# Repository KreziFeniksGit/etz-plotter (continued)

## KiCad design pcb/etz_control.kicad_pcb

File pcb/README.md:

# Main control PCB (KiCad 10)

**Current design (23 Oct): three split single-sided boards, hand-routed - see split_boards.md** (drivers/, power/, controller/).
The single-board files below (etz_control.*) are the earlier versions, kept for reference.

**Current version: HOME (single-sided, toner transfer), placed, NOT routed - Egor routes it by hand (22 Oct).**
`build_pcb.py` has `HOME = True`: 169 x 136 mm, copper on the bottom only, traces >= 0.5 mm (signals 0.6, 5 V 1.2, motors 1.0,
power 2.0), 0.6 mm gaps (0.8 around power), oval 1.7 x 2.6 pads with 1.0 mm drills on 2.54 mm rows (round 1.9 on the 2x5 header),
1206 parts and the SMD parts on the copper side, IRLZ44N (TO-220) instead of the SOT-23 MOSFET. DRC with these rules: 0 errors.
The auto-router could not do it single-sided (66 wire jumpers + 70 drilled holes and still 9 open): route by hand.
Tips for routing by hand:
- Route power first (VBAT, VDRIVE, GND), then motors, then signals. Leave GND for a ground pour at the end (Place > Zone, B.Cu).
- Where a trace cannot cross, use a wire jumper on the top side: drill two holes, insulated wire, solder underneath.
- **You may swap ESP32 pins** to remove crossings (the firmware is not written yet). Allowed GPIOs: 1, 2, 4..18, 21, 39..42, 47
  (38 only if your board is v1.0). A_IO and VBAT_SENSE must stay on GPIO 1..10 (ADC1). Never use 0, 3, 19, 20, 26..37, 43..46, 48.
  Tell Claude which pins you moved: wiring.md, the schematic and the firmware follow.
- For printing: File > Plot, layer B.Cu + Edge.Cuts, PDF, black, scale 1:1, drill marks "small"; NOT mirrored for the bottom layer
  (the toner transfer itself mirrors it the right way).

| File | What |
|---|---|
| `bom.md` | every part on and off the board, the power tree, what is still VERIFY |
| `build_pcb.py` | parts, nets (from `wiring.md`), placement, JLCPCB rules, net classes -> routes with Freerouting -> GND pours + stitching vias |
| `etz_control.kicad_pcb` | the board (open it in KiCad) |
| `etz_control.kicad_sch` + `etz_control_schematic.pdf` | **full connection schematic** (KiCad + PDF), A2; `schematic_preview.png` |
| `build_sch.py` | makes the schematic from the same parts/nets as `build_pcb.py`, then checks: KiCad netlist == board nets, ERC, PDF |
| `etz.kicad_sym`, `etz.pretty/`, `sym-lib-table`, `fp-lib-table` | project library: symbols + footprints of the plug-in modules (ESP32-S3-DevKitC-1, TMC2209, Mini560 Pro, BSS138) |
| `etz_control_gerbers_jlcpcb.zip` | upload this to JLCPCB / PCBWay (Gerbers + drill), 2 layers, 1.6 mm, 1 oz |
| `render_top.png`, `render_bottom.png`, `copper.svg` | pictures |
| `drc.json` | KiCad design-rule check result |

Rebuild: `"C:\Program Files\KiCad\10.0\bin\python.exe" pcb\build_pcb.py` (about 3 min: routing), then
`kicad-cli pcb drc --refill-zones pcb\etz_control.kicad_pcb`, then the Gerber / drill export (see the end of this file).
Routing needs Java 25 + Freerouting 2.5 in `%USERPROFILE%\tools` (`jre25\`, `freerouting-2.5.0.jar`).

## v1.0 (22 Oct): 130 x 105 mm, 2 layers, 69 footprints, 58 nets, fully routed
DRC: 0 unconnected, 0 clearance errors. Remaining warnings (accepted): the XT60 / XT30 outlines cross the board edge on purpose
(the plug goes in from the edge); 3 GND pins (U1B pin 1, U8A/U8B pin 4) have 1 thermal spoke instead of 2 - they are also
joined by a trace.

## Review checklist (from JLCPCB / Altium / DigiKey / TI layout guides) and how this board meets it
| Check | Status |
|---|---|
| DRC set to the fab's limits, not KiCad defaults | min track / clearance 0.15, via 0.6 / 0.3 drill, hole-to-hole 0.5, copper to edge 0.4 (JLCPCB standard is 0.127 / 0.3) |
| Trace width by current (IPC-2152, ~10 C rise) | VBAT / VDRIVE 1.5 mm (~4 A), 5 V rails 1.0 mm, motor phases 0.8 mm (0.9 A), signals 0.3 mm |
| Bulk capacitor close to each driver's VM | C1..C4 100 uF directly below each TMC2209 |
| Servo rail spike capacitor | C5 470 uF + C6 100 nF next to the servo rail |
| Solid ground | GND pour on both layers, 44 stitching vias, thermal reliefs for hand soldering |
| Footprints match the real parts | KiCad standard library; module pinouts VERIFY (below) |
| Polarity marked | + on electrolytics and XT plugs, K bar on diodes, pin 1 marks on headers |
| Labels | every connector named on the silkscreen; board name + version |
| Test points | 3V3, +5V, +5V servo, GND |
| Mounting | 4x M3 holes, 4 mm from the corners |
| Protection | main 5 A fuse inline; 0.5 A PTC on connector C's V pin; flyback diode on the magnet; EN pull-up keeps drivers off at boot; gate pull-down keeps the magnet off |
| Auto-router output reviewed | 0 unrouted; power traces checked wide; see renders |
| Not applicable | antenna keep-out (the radio is never used), impedance control, fiducials (hand assembly) |

## VERIFY before ordering (guesses about bought modules)
ESP32-S3-DevKitC-1 pin rows (22.86) and pinout revision (v1.1 has its RGB LED on GPIO38 = TOF XSHUT here); TMC2209 V1.3
pin order; Mini560 Pro pad positions (IN at one end, OUT 25.4 mm away - measure yours); motor
connector pin order (match your motor cables); XT60 / XT30 genders. A photo of each module with a ruler settles them.

## Export commands
```
kicad-cli pcb export gerbers --layers F.Cu,B.Cu,F.Mask,B.Mask,F.Silkscreen,B.Silkscreen,Edge.Cuts --subtract-soldermask -o pcb/fab/ pcb/etz_control.kicad_pcb
kicad-cli pcb export drill --format excellon --excellon-units mm --excellon-separate-th -o pcb/fab/ pcb/etz_control.kicad_pcb
```

## Making your own PCB from the schematic
Open `etz_control.kicad_pro`, open the schematic, then Tools > Update PCB from Schematic (F8) into a NEW board (or delete the
footprints in the existing one first: the generated board uses two sockets per module, the schematic one footprint per module).
Footprints are already assigned. Net classes (track widths) are in the project: Power 1.5 mm, Rail5V 1.0, Motor 0.8, signals 0.3.

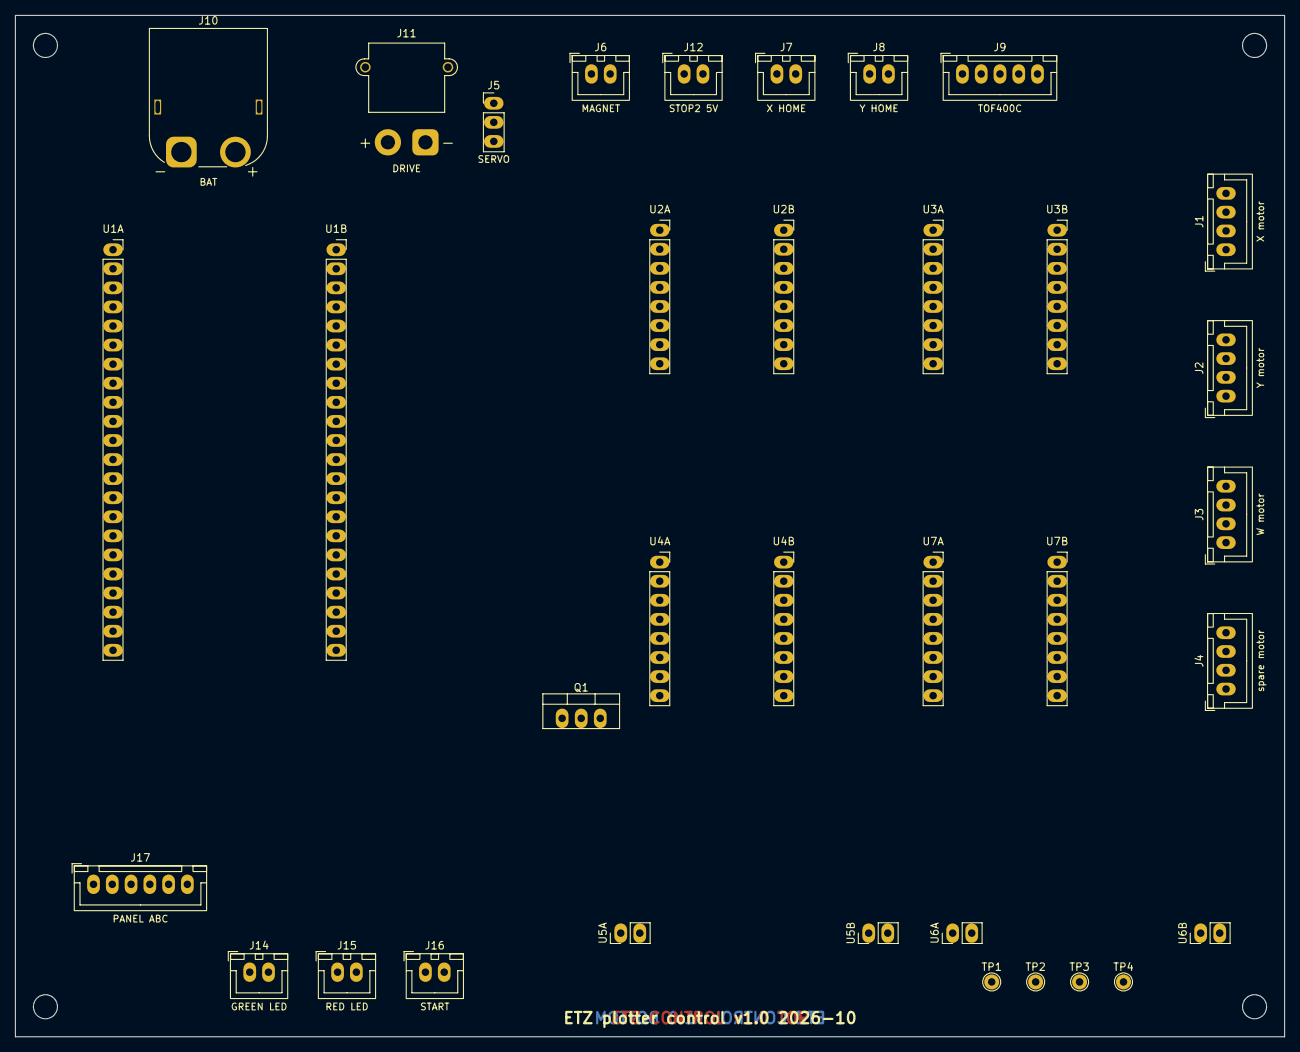
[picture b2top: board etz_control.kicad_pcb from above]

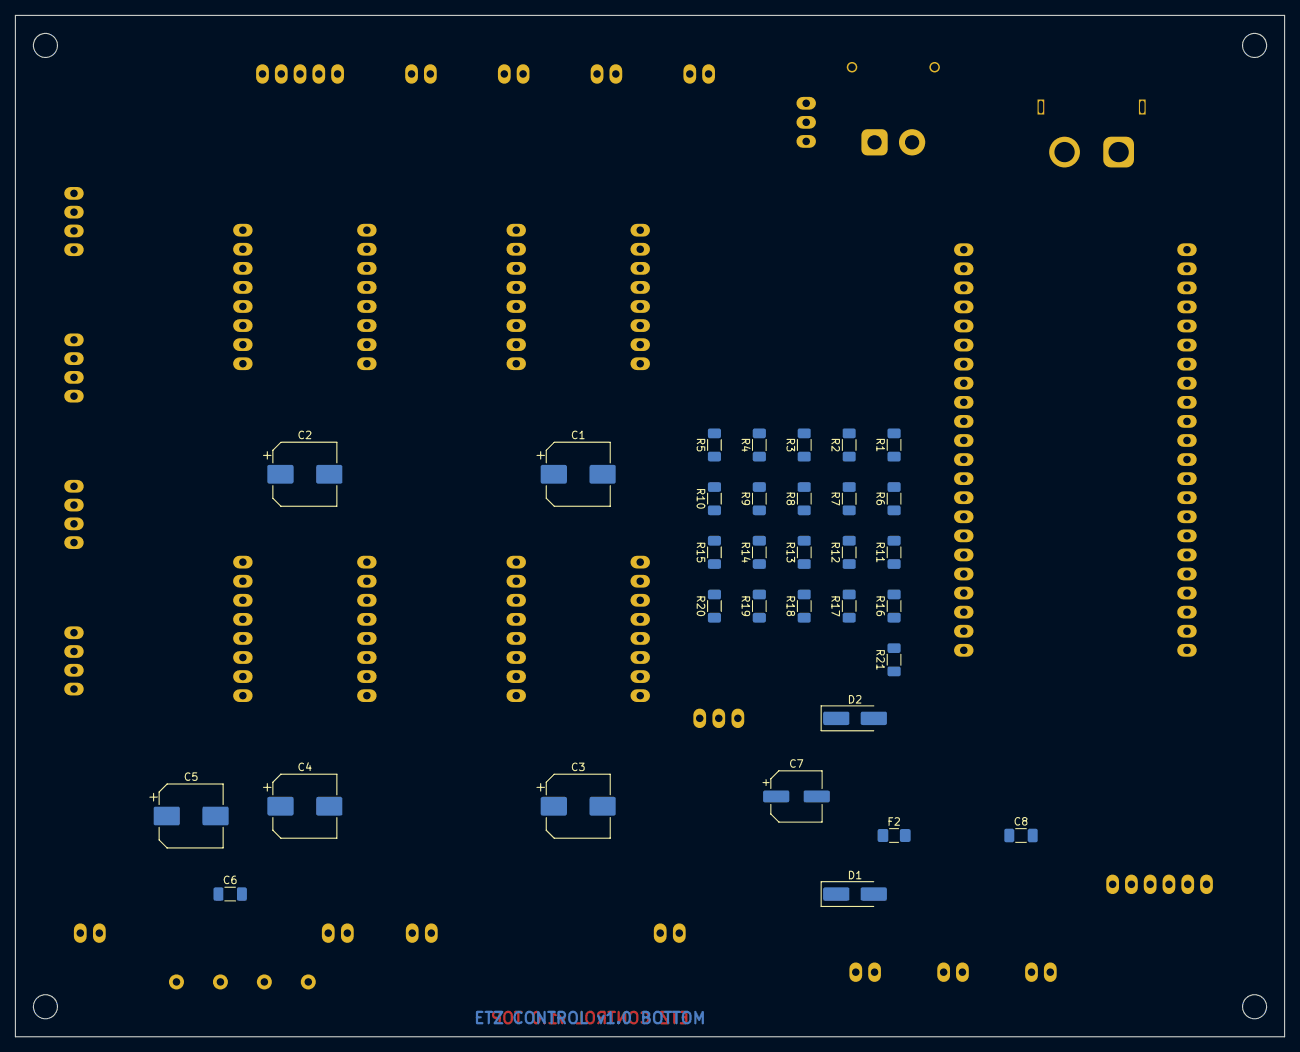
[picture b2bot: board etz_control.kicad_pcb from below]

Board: 2 copper layers, 169.0 x 136.0 mm, 71 parts (32 on the bottom side), 58 nets, no tracks yet.

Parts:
C1, C2, C3, C4: 100uF 35V; CP_Elec_8x10
C5: 470uF 16V; CP_Elec_8x10
C6: 100nF; C_1206_3216Metric_Pad1.33x1.80mm_HandSolder
C7: 100uF 10V; CP_Elec_6.3x7.7
C8: 10nF; C_1206_3216Metric_Pad1.33x1.80mm_HandSolder
D1: SS34; D_SMA_Handsoldering
D2: SS34 flyback; D_SMA_Handsoldering
F2: PTC 0.5A; Fuse_1206_3216Metric_Pad1.42x1.75mm_HandSolder
H1, H2, H3, H4: M3; MountingHole_3.2mm_M3
J1: X motor; JST_XH_B4B-XH-A_1x04_P2.50mm_Vertical
J2: Y motor; JST_XH_B4B-XH-A_1x04_P2.50mm_Vertical
J3: W motor; JST_XH_B4B-XH-A_1x04_P2.50mm_Vertical
J4: spare motor; JST_XH_B4B-XH-A_1x04_P2.50mm_Vertical
J5: SERVO; PinHeader_1x03_P2.54mm_Vertical
J6: MAGNET; JST_XH_B2B-XH-A_1x02_P2.50mm_Vertical
J7: X HOME; JST_XH_B2B-XH-A_1x02_P2.50mm_Vertical
J8: Y HOME; JST_XH_B2B-XH-A_1x02_P2.50mm_Vertical
J9: TOF400C; JST_XH_B5B-XH-A_1x05_P2.50mm_Vertical
J10: BAT; AMASS_XT60PW-M_1x02_P7.20mm_Horizontal
J11: DRIVE; AMASS_XT30PW-M_1x02_P2.50mm_Horizontal
J12: STOP2 5V; JST_XH_B2B-XH-A_1x02_P2.50mm_Vertical
J14: GREEN LED; JST_XH_B2B-XH-A_1x02_P2.50mm_Vertical
J15: RED LED; JST_XH_B2B-XH-A_1x02_P2.50mm_Vertical
J16: START; JST_XH_B2B-XH-A_1x02_P2.50mm_Vertical
J17: PANEL ABC; JST_XH_B6B-XH-A_1x06_P2.50mm_Vertical
Q1: IRLZ44N; TO-220-3_Vertical
R1, R3, R15: 100k; R_1206_3216Metric_Pad1.30x1.75mm_HandSolder
R2: 22k; R_1206_3216Metric_Pad1.30x1.75mm_HandSolder
R4: 15k; R_1206_3216Metric_Pad1.30x1.75mm_HandSolder
R5, R7, R10, R11, R19: 10k; R_1206_3216Metric_Pad1.30x1.75mm_HandSolder
R6, R20, R21: 20k; R_1206_3216Metric_Pad1.30x1.75mm_HandSolder
R8, R9, R18: 1k; R_1206_3216Metric_Pad1.30x1.75mm_HandSolder
R12, R13: 4.7k; R_1206_3216Metric_Pad1.30x1.75mm_HandSolder
R14: 100R; R_1206_3216Metric_Pad1.30x1.75mm_HandSolder
R16: 1.5k 0.25W; R_1206_3216Metric_Pad1.30x1.75mm_HandSolder
R17: 220R; R_1206_3216Metric_Pad1.30x1.75mm_HandSolder
TP1: 3V3; TestPoint_THTPad_D2.0mm_Drill1.0mm
TP2: +5V; TestPoint_THTPad_D2.0mm_Drill1.0mm
TP3: +5VS; TestPoint_THTPad_D2.0mm_Drill1.0mm
TP4: GND; TestPoint_THTPad_D2.0mm_Drill1.0mm
U1A: ESP32-S3 J1; PinSocket_1x22_P2.54mm_Vertical
U1B: ESP32-S3 J3; PinSocket_1x22_P2.54mm_Vertical
U2A: TMC2209 X left; PinSocket_1x08_P2.54mm_Vertical
U2B: TMC2209 X right; PinSocket_1x08_P2.54mm_Vertical
U3A: TMC2209 Y left; PinSocket_1x08_P2.54mm_Vertical
U3B: TMC2209 Y right; PinSocket_1x08_P2.54mm_Vertical
U4A: TMC2209 W left; PinSocket_1x08_P2.54mm_Vertical
U4B: TMC2209 W right; PinSocket_1x08_P2.54mm_Vertical
U5A: Mini560 Pro 5V logic IN; PinHeader_1x02_P2.54mm_Vertical
U5B: Mini560 Pro 5V logic OUT; PinHeader_1x02_P2.54mm_Vertical
U6A: Mini560 Pro 5V servo IN; PinHeader_1x02_P2.54mm_Vertical
U6B: Mini560 Pro 5V servo OUT; PinHeader_1x02_P2.54mm_Vertical
U7A: TMC2209 S left; PinSocket_1x08_P2.54mm_Vertical
U7B: TMC2209 S right; PinSocket_1x08_P2.54mm_Vertical

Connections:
3V3: J9.1, R10.2, R11.2, R12.2, R13.2, TP1.1, U1A.1, U1A.2, U2B.7, U3A.2, U3B.7, U4A.3, U4B.7, U7A.2, U7A.3, U7B.7
5V_ESP: D1.1, U1A.21
+5V: C7.1, D1.2, F2.1, J12.1, TP2.1, U5B.1
+5VS: C5.1, C6.1, J5.2, TP3.1, U6B.1
A_IO: C8.1, R7.2, R21.1, U1B.4
A_SIG: J17.1, R7.1
B_IO: R5.2, R6.1, U1A.16
B_SIG: J17.2, R5.1
C_RX: J17.4, R19.1
C_TX: J17.3, R18.2
C_V: F2.2, J17.5
DRV_EN: R10.1, U1A.19, U2A.1, U3A.1, U4A.1, U7A.1
GND: C1.2, C2.2, C3.2, C4.2, C5.2, C6.2, C7.2, C8.2, J5.3, J7.2, J8.2, J9.2, J10.1, J11.2, J14.2, J15.2, J16.2, J17.6, Q1.3, R2.2, R4.2, R6.2, R15.2, R20.2, R21.2, TP4.1, U1A.22, U1B.1, U1B.21, U1B.22, U2A.2, U2A.3, U2B.2, U2B.8, U3A.3, U3B.2, U3B.8, U4A.2, U4B.2, U4B.8, U5A.2, U5B.2, U6A.2, U6B.2, U7B.2, U7B.8
LEDG_A: J14.1, R16.2
LEDR_A: J15.1, R17.2
LEDR_IO: R17.1, U1B.6
MAG5: D2.1, J6.1, J12.2
MAG_G: Q1.1, R14.2, R15.1
MAG_IO: R14.1, U1B.18
MAG_SW: D2.2, J6.2, Q1.2
SCL: J9.4, R13.1, U1A.18
SDA: J9.3, R12.1, U1A.17
SERVO_IO: R9.1, U1A.20
SERVO_SIG: J5.1, R9.2
START: J16.1, U1B.7
STOP_SENSE: R1.2, R2.1, U1B.17
S_1A: J4.1, U7B.5
S_1B: J4.2, U7B.6
S_2A: J4.3, U7B.4
S_2B: J4.4, U7B.3
TMC_TX: R8.1, U1A.8
TMC_UART: R8.2, U1A.9, U2A.4, U3A.4, U4A.4, U7A.4
TOF_XSHUT: J9.5, R11.1, U1B.10
U1_RX: R19.2, R20.1, U1A.11
U1_TX: R18.1, U1A.10
VBAT: J10.2, R3.1, U5A.1
VBAT_SENSE: R3.2, R4.1, U1B.5
VDRIVE: C1.1, C2.1, C3.1, C4.1, J11.1, R1.1, R16.1, U2B.1, U3B.1, U4B.1, U6A.1, U7B.1
W_1A: J3.1, U4B.5
W_1B: J3.2, U4B.6
W_2A: J3.3, U4B.4
W_2B: J3.4, U4B.3
W_DIR: U1A.15, U4A.8
W_STEP: U1A.12, U4A.7
X_1A: J1.1, U2B.5
X_1B: J1.2, U2B.6
X_2A: J1.3, U2B.4
X_2B: J1.4, U2B.3
X_DIR: U1A.5, U2A.8
X_HOME: J7.1, U1B.9
X_STEP: U1A.4, U2A.7
Y_1A: J2.1, U3B.5
Y_1B: J2.2, U3B.6
Y_2A: J2.3, U3B.4
Y_2B: J2.4, U3B.3
Y_DIR: U1A.7, U3A.8
Y_HOME: J8.1, U1B.8
Y_STEP: U1A.6, U3A.7

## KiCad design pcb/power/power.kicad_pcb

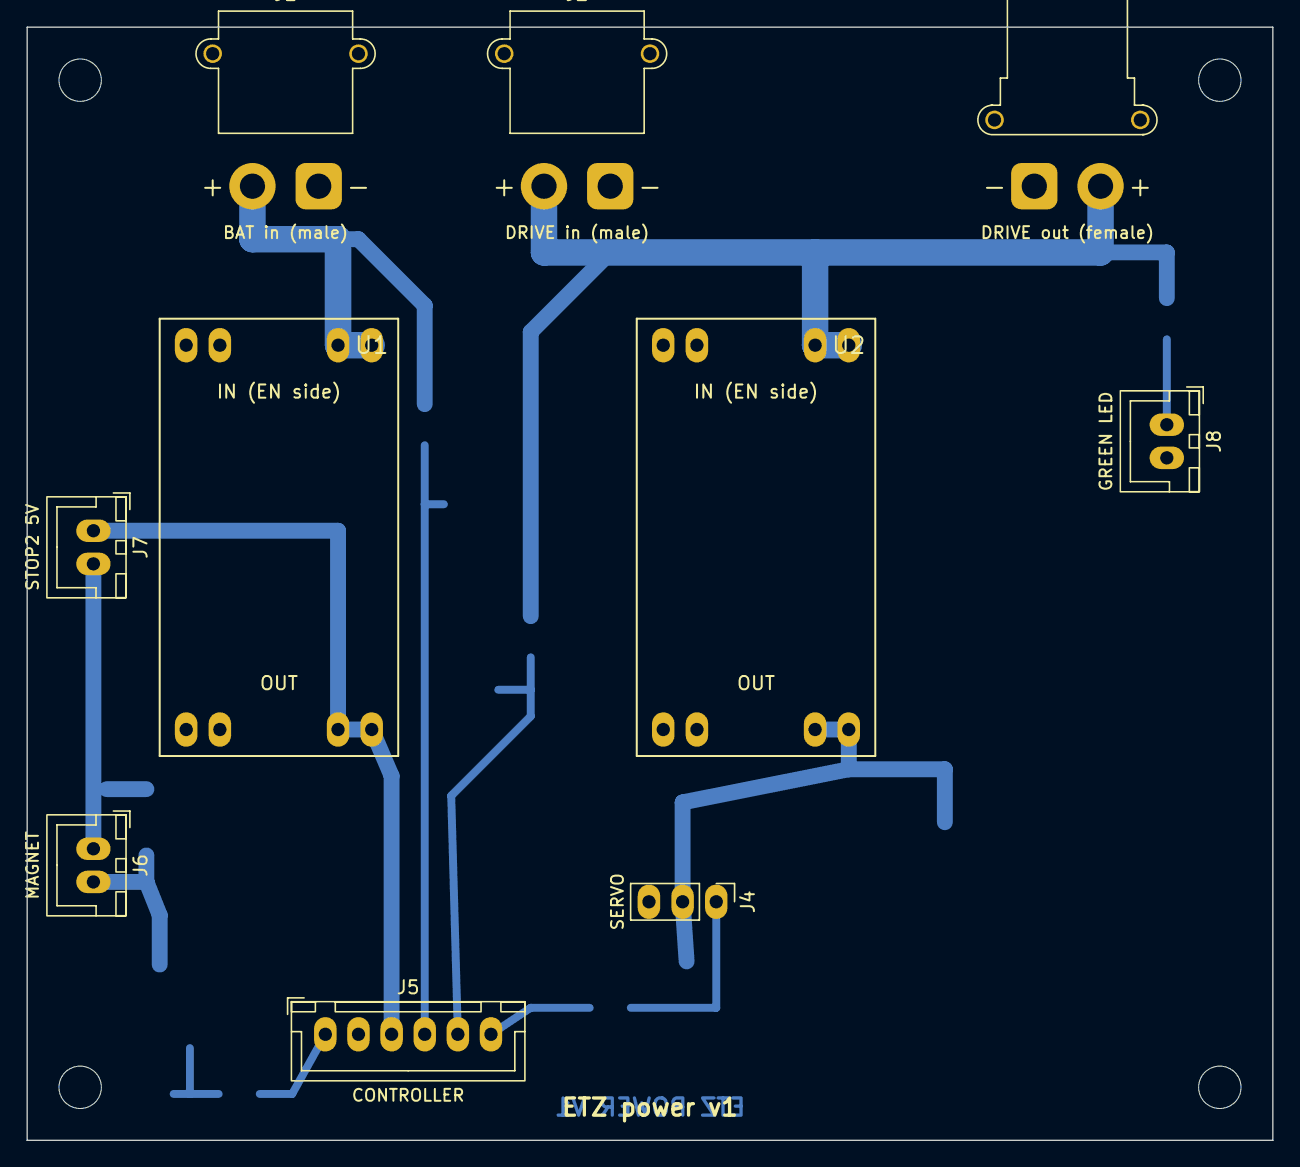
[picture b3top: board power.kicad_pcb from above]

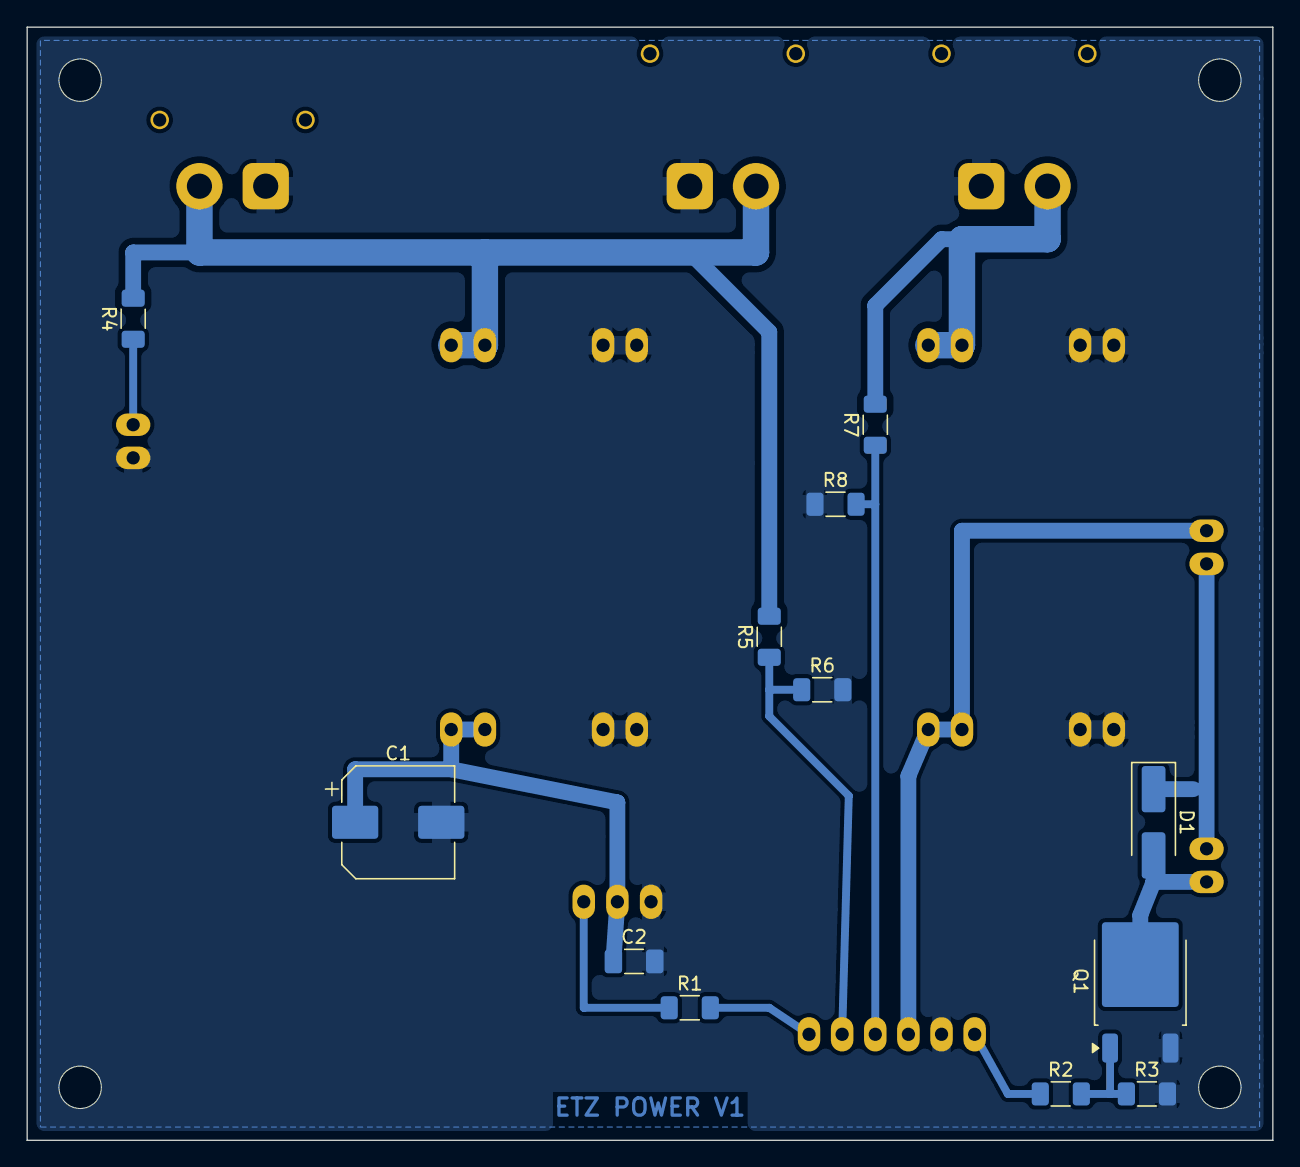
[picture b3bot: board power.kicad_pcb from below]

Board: 2 copper layers, 94.0 x 84.0 mm, 26 parts (12 on the bottom side), 14 nets.

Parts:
C1: 470uF 16V; CP_Elec_8x10
C2: 100nF; C_1206_3216Metric_Pad1.33x1.80mm_HandSolder
D1: SS34 flyback; D_SMA_Handsoldering
H1, H2, H3, H4: M3; MountingHole_3.2mm_M3
J1: BAT in (male); AMASS_XT30PW-M_1x02_P2.50mm_Horizontal
J2: DRIVE in (male); AMASS_XT30PW-M_1x02_P2.50mm_Horizontal
J3: DRIVE out (female); AMASS_XT30PW-F_1x02_P2.50mm_Horizontal
J4: SERVO; PinHeader_1x03_P2.54mm_Vertical
J5: CONTROLLER; JST_XH_B6B-XH-A_1x06_P2.50mm_Vertical
J6: MAGNET; JST_XH_B2B-XH-A_1x02_P2.50mm_Vertical
J7: STOP2 5V; JST_XH_B2B-XH-A_1x02_P2.50mm_Vertical
J8: GREEN LED; JST_XH_B2B-XH-A_1x02_P2.50mm_Vertical
Q1: 100N03A; TO-252-2
R1: 1k; R_1206_3216Metric_Pad1.30x1.75mm_HandSolder
R2: 100R; R_1206_3216Metric_Pad1.30x1.75mm_HandSolder
R3, R5, R7: 100k; R_1206_3216Metric_Pad1.30x1.75mm_HandSolder
R4: 1.5k; R_1206_3216Metric_Pad1.30x1.75mm_HandSolder
R6: 22k; R_1206_3216Metric_Pad1.30x1.75mm_HandSolder
R8: 15k; R_1206_3216Metric_Pad1.30x1.75mm_HandSolder
U1: Mini560 Pro 5V logic
U2: Mini560 Pro 5V servo

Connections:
+5V: J5.3, J7.1, U1.3
+5VS: C1.1, C2.1, J4.2, U2.3
GND: C1.2, C2.2, J1.1, J2.1, J3.1, J4.3, J5.2, J8.2, Q1.3, R3.2, R6.2, R8.1, U1.2, U1.4, U2.2, U2.4
LEDG_A: J8.1, R4.1
MAG5: D1.1, J6.1, J7.2
MAG_G: Q1.1, R2.2, R3.1
MAG_IO: J5.1, R2.1
MAG_SW: D1.2, J6.2, Q1.2
SERVO_IO: J5.6, R1.2
SERVO_SIG: J4.1, R1.1
STOP_SENSE: J5.5, R5.1, R6.1
VBAT: J1.2, R7.2, U1.1
VBAT_SENSE: J5.4, R7.1, R8.2
VDRIVE: J2.2, J3.2, R4.2, R5.2, U2.1

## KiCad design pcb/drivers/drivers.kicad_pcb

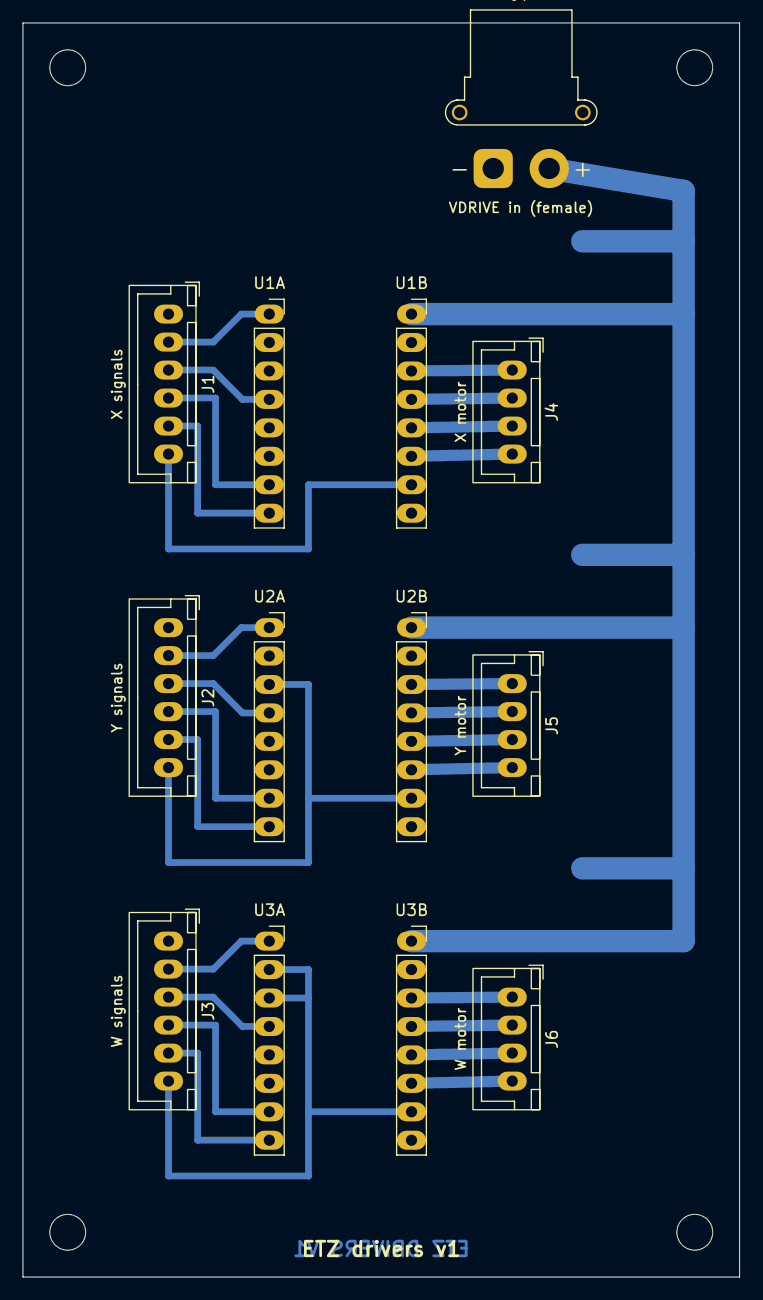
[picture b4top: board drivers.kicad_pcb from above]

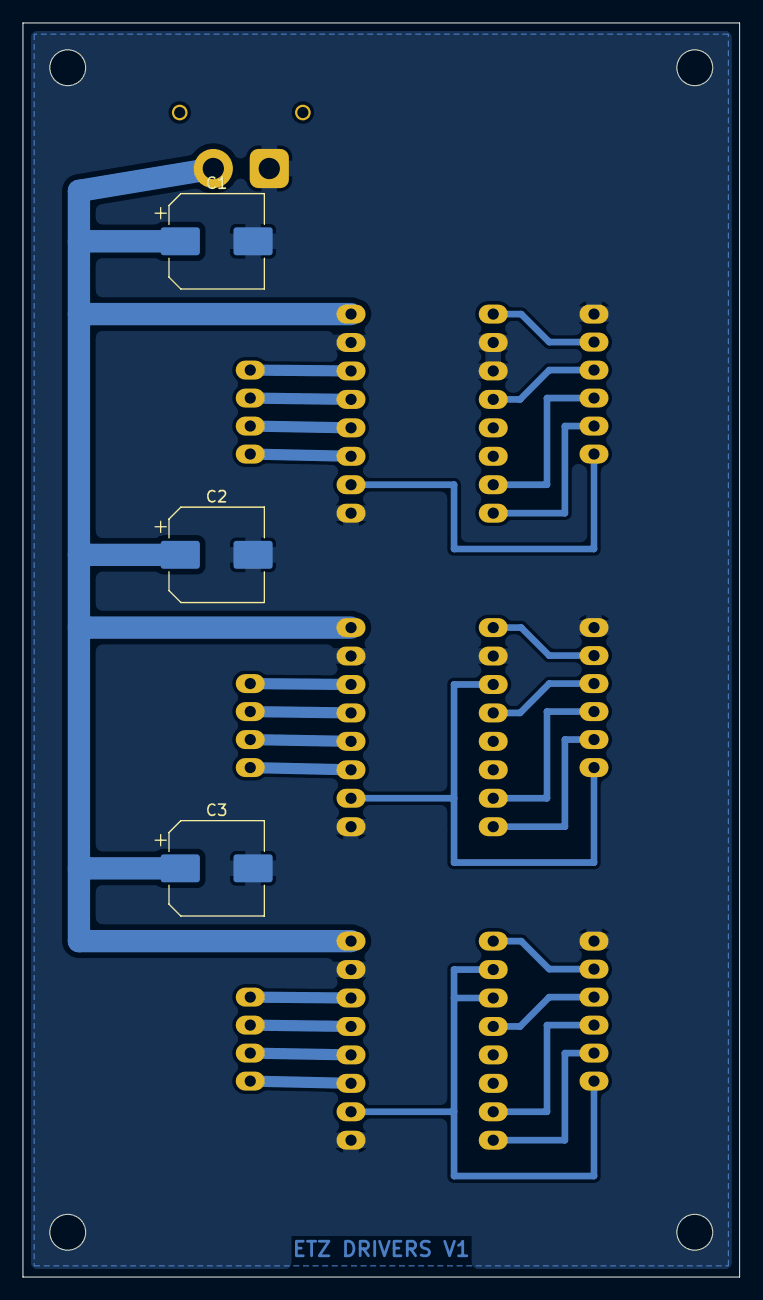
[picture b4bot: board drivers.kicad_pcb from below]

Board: 2 copper layers, 64.0 x 112.0 mm, 20 parts (3 on the bottom side), 29 nets.

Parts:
C1, C2, C3: 100uF 25V; CP_Elec_8x10
H1, H2, H3, H4: M3; MountingHole_3.2mm_M3
J1: X signals; JST_XH_B6B-XH-A_1x06_P2.50mm_Vertical
J2: Y signals; JST_XH_B6B-XH-A_1x06_P2.50mm_Vertical
J3: W signals; JST_XH_B6B-XH-A_1x06_P2.50mm_Vertical
J4: X motor; JST_XH_B4B-XH-A_1x04_P2.50mm_Vertical
J5: Y motor; JST_XH_B4B-XH-A_1x04_P2.50mm_Vertical
J6: W motor; JST_XH_B4B-XH-A_1x04_P2.50mm_Vertical
J7: VDRIVE in (female); AMASS_XT30PW-F_1x02_P2.50mm_Horizontal
U1A, U1B: TMC2209 X; PinSocket_1x08_P2.54mm_Vertical
U2A, U2B: TMC2209 Y; PinSocket_1x08_P2.54mm_Vertical
U3A, U3B: TMC2209 W; PinSocket_1x08_P2.54mm_Vertical

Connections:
GND: C1.2, C2.2, C3.2, J1.1, J2.1, J3.1, J7.1, U1A.2, U1A.3, U1B.2, U1B.8, U2A.2, U2B.2, U2B.8, U3B.2, U3B.8
VDRIVE: C1.1, C2.1, C3.1, J7.2, U1B.1, U2B.1, U3B.1
W_1A: J6.3, U3B.5
W_1B: J6.4, U3B.6
W_2A: J6.2, U3B.4
W_2B: J6.1, U3B.3
W_3V3: J3.6, U3A.2, U3A.3, U3B.7
W_DIR: J3.5, U3A.8
W_EN: J3.2, U3A.1
W_STEP: J3.4, U3A.7
W_UART: J3.3, U3A.4
X_1A: J4.3, U1B.5
X_1B: J4.4, U1B.6
X_2A: J4.2, U1B.4
X_2B: J4.1, U1B.3
X_3V3: J1.6, U1B.7
X_DIR: J1.5, U1A.8
X_EN: J1.2, U1A.1
X_STEP: J1.4, U1A.7
X_UART: J1.3, U1A.4
Y_1A: J5.3, U2B.5
Y_1B: J5.4, U2B.6
Y_2A: J5.2, U2B.4
Y_2B: J5.1, U2B.3
Y_3V3: J2.6, U2A.3, U2B.7
Y_DIR: J2.5, U2A.8
Y_EN: J2.2, U2A.1
Y_STEP: J2.4, U2A.7
Y_UART: J2.3, U2A.4

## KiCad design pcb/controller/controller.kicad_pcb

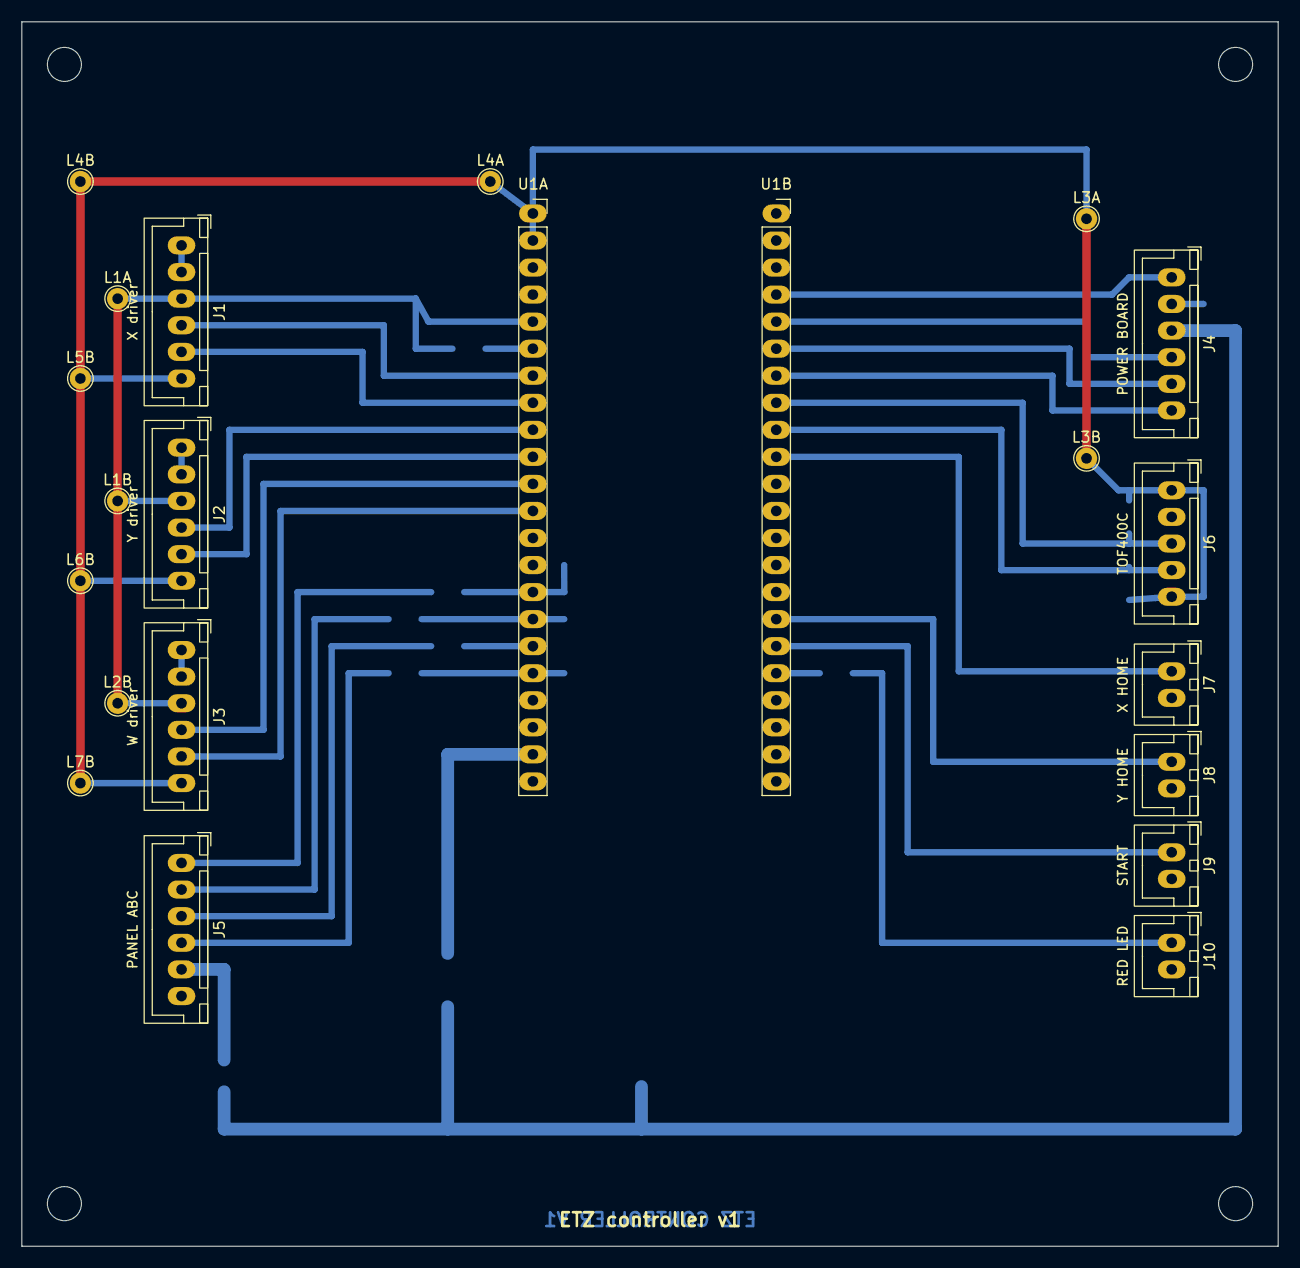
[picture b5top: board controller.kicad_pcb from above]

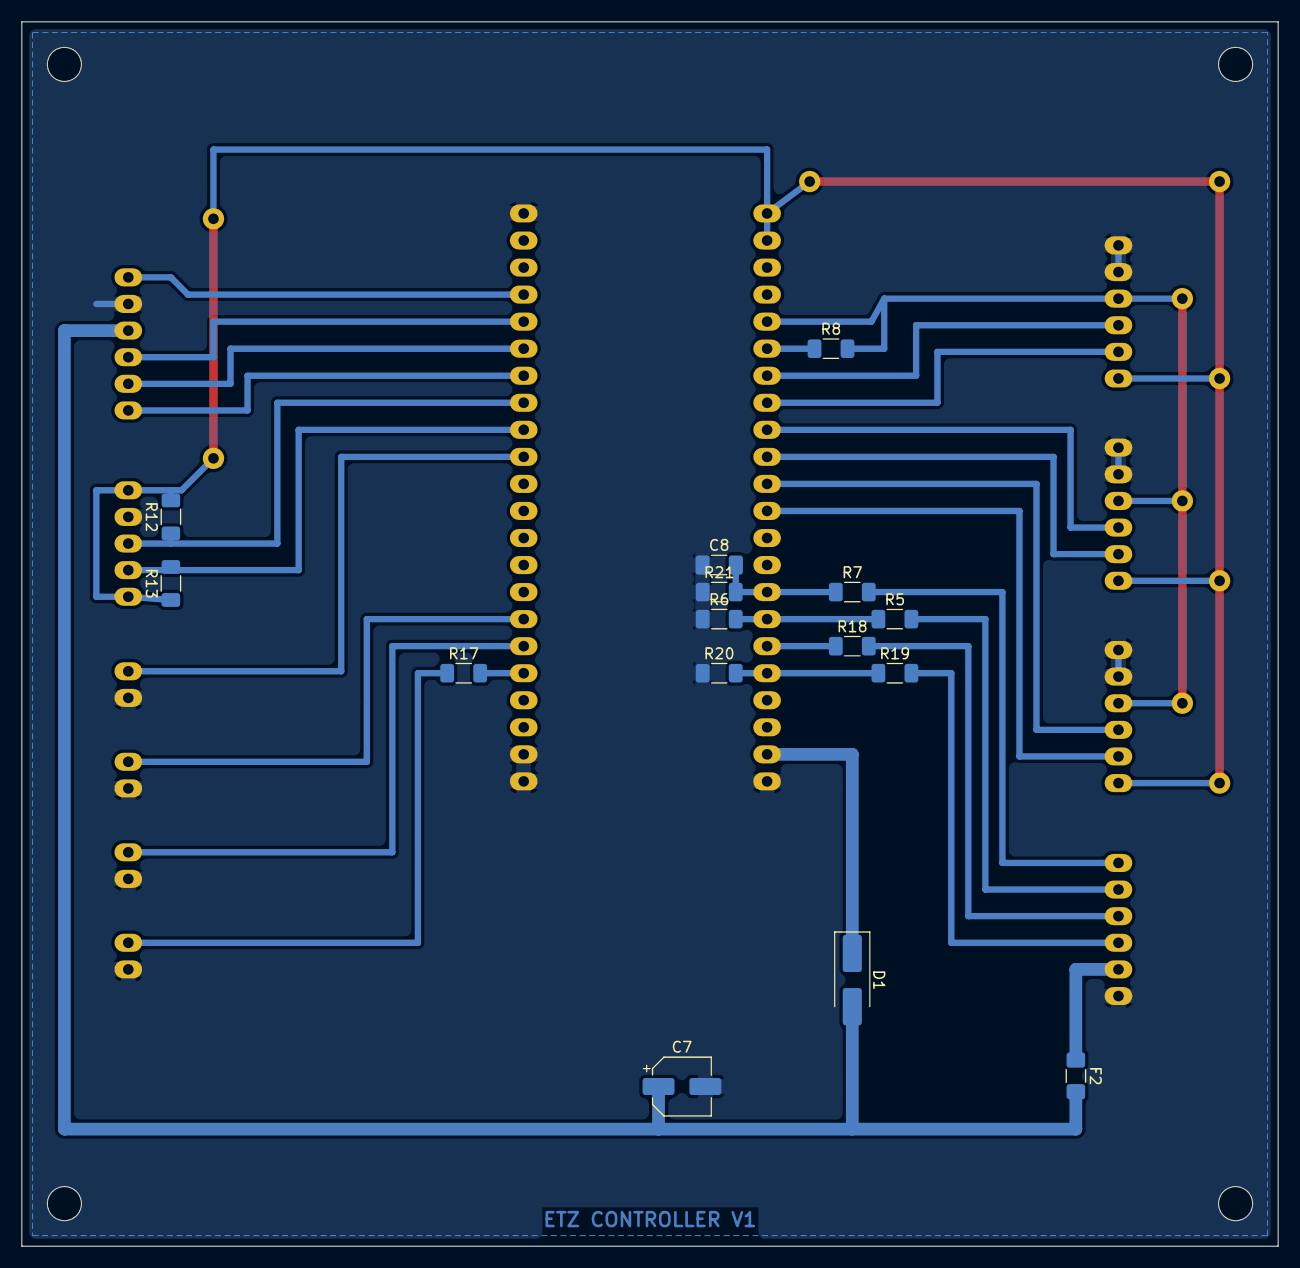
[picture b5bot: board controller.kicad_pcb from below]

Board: 2 copper layers, 118.0 x 115.0 mm, 41 parts (15 on the bottom side), 32 nets.

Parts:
C7: 100uF 10V; CP_Elec_5x5.4
C8: 10nF; C_1206_3216Metric_Pad1.33x1.80mm_HandSolder
D1: SS34; D_SMA_Handsoldering
F2: PTC 0.5A; Fuse_1206_3216Metric_Pad1.42x1.75mm_HandSolder
H1, H2, H3, H4: M3; MountingHole_3.2mm_M3
J1: X driver; JST_XH_B6B-XH-A_1x06_P2.50mm_Vertical
J2: Y driver; JST_XH_B6B-XH-A_1x06_P2.50mm_Vertical
J3: W driver; JST_XH_B6B-XH-A_1x06_P2.50mm_Vertical
J4: POWER BOARD; JST_XH_B6B-XH-A_1x06_P2.50mm_Vertical
J5: PANEL ABC; JST_XH_B6B-XH-A_1x06_P2.50mm_Vertical
J6: TOF400C; JST_XH_B5B-XH-A_1x05_P2.50mm_Vertical
J7: X HOME; JST_XH_B2B-XH-A_1x02_P2.50mm_Vertical
J8: Y HOME; JST_XH_B2B-XH-A_1x02_P2.50mm_Vertical
J9: START; JST_XH_B2B-XH-A_1x02_P2.50mm_Vertical
J10: RED LED; JST_XH_B2B-XH-A_1x02_P2.50mm_Vertical
L1A, L1B, L2B, L3A, L3B, L4A, L4B, L5B, L6B, L7B: wire link; TestPoint_THTPad_D2.0mm_Drill1.0mm
R5, R7, R19: 10k; R_1206_3216Metric_Pad1.30x1.75mm_HandSolder
R6, R20, R21: 20k; R_1206_3216Metric_Pad1.30x1.75mm_HandSolder
R8, R18: 1k; R_1206_3216Metric_Pad1.30x1.75mm_HandSolder
R12, R13: 4.7k; R_1206_3216Metric_Pad1.30x1.75mm_HandSolder
R17: 220R; R_1206_3216Metric_Pad1.30x1.75mm_HandSolder
U1A: ESP32-S3 left (J1); PinSocket_1x22_P2.54mm_Vertical
U1B: ESP32-S3 right (J3); PinSocket_1x22_P2.54mm_Vertical

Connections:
3V3: J1.6, J2.6, J3.6, J6.1, J6.5, L3A.1, L3B.1, L4A.1, L4B.1, L5B.1, L6B.1, L7B.1, R12.2, R13.1, U1A.1, U1A.2
5V_ESP: D1.1, U1A.21
+5V: C7.1, D1.2, F2.2, J4.3
A_IO: C8.2, R7.1, R21.2, U1A.15
A_SIG: J5.1, R7.2
B_IO: R5.1, R6.2, U1A.16
B_SIG: J5.2, R5.2
C_RX: J5.4, R19.2
C_TX: J5.3, R18.2
C_V: F2.1, J5.5
GND: C7.2, C8.1, J1.1, J1.2, J2.1, J2.2, J3.1, J3.2, J4.2, J5.6, J6.2, J7.2, J8.2, J9.2, J10.2, R6.1, R20.1, R21.1, U1A.22, U1B.1, U1B.21, U1B.22
LEDR_A: J10.1, R17.1
LEDR_IO: R17.2, U1B.18
MAG_IO: J4.1, U1B.4
SCL: J6.4, R13.2, U1B.9
SDA: J6.3, R12.1, U1B.8
SERVO_IO: J4.6, U1B.7
START: J9.1, U1B.17
STOP_SENSE: J4.5, U1B.6
TMC_TX: R8.1, U1A.6
TMC_UART: J1.3, J2.3, J3.3, L1A.1, L1B.1, L2B.1, R8.2, U1A.5
U1_RX: R19.1, R20.2, U1A.18
U1_TX: R18.1, U1A.17
VBAT_SENSE: J4.4, U1B.5
W_DIR: J3.5, U1A.12
W_STEP: J3.4, U1A.11
X_DIR: J1.5, U1A.8
X_HOME: J7.1, U1B.10
X_STEP: J1.4, U1A.7
Y_DIR: J2.5, U1A.10
Y_HOME: J8.1, U1B.16
Y_STEP: J2.4, U1A.9

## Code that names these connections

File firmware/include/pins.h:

// ESP32-S3 pin map of the split controller board (wiring.md section 2, pcb/split_boards.md)
#pragma once

// TMC2209 single-wire UART bus (all three drivers): RX direct, TX through R8 1k onto the same wire
constexpr int PIN_TMC_RX = 5;
constexpr int PIN_TMC_TX = 6;

// STEP / DIR. Egor's cables cross X and wrist (controller J1 -> driver J3, J3 -> J1; 25 Oct), so the
// X driver gets the controller's J3 pins (18 / 8) and the wrist driver gets J1 (7 / 15). Swapped here, not in the cables.
constexpr int PIN_X_STEP = 18, PIN_X_DIR = 8;
constexpr int PIN_Y_STEP = 16, PIN_Y_DIR = 17;
constexpr int PIN_W_STEP = 7,  PIN_W_DIR = 15;     // W = wrist (NEMA17 pancake)

// Driver EN pins are tied to GND on the controller board: drivers are always enabled.
// They are switched off over UART (TOFF = 0); the stop button cuts their power (VM).

// Other pins (not used by this bench test yet)
constexpr int PIN_MAG_IO = 1, PIN_VBAT_SENSE = 2, PIN_STOP_SENSE = 42, PIN_SERVO = 41;
constexpr int PIN_SDA = 40, PIN_SCL = 39;
constexpr int PIN_X_HOME = 38, PIN_Y_HOME = 48, PIN_START = 47, PIN_LED_RED = 21;   // 38 / 48: inputs only
constexpr int PIN_A_IO = 9, PIN_B_IO = 10, PIN_U1_TX = 11, PIN_U1_RX = 12;

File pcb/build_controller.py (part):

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  left row : 4 not used, 5 TMC_UART (RX), 6 TMC_TX (through R8 1k onto the same wire), 7 X_STEP, 15 X_DIR, 16 Y_STEP,
             17 Y_DIR, 18 W_STEP, 8 W_DIR, 9 A_IO (ADC), 10 B_IO, 11 U1_TX (connector C), 12 U1_RX, 13/14 not used
  right row: 1 MAG_IO, 2 VBAT_SENSE (ADC), 42 STOP_SENSE, 41 SERVO_IO, 40 SDA, 39 SCL, 38 X_HOME, 48 Y_HOME,
             47 START, 21 LEDR_IO   (38 / 48: one of them is the board's RGB LED data pin - used as inputs only: harmless)
Driver EN pins are tied to GND here (drivers always enabled; the firmware turns them off over UART, the stop button cuts
their power). TOF XSHUT is tied to 3V3 (sensor always on).
Connectors (all <= 6 pins, straight 1:1 cables):
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        b.track([p(r, 4), (LANE[ax + '_STEP'], p(r, 4)[1]), (LANE[ax + '_STEP'], esp(ps)[1]), esp(ps)], ax + '_STEP', SIG)
        b.track([p(r, 5), (LANE[ax + '_DIR'], p(r, 5)[1]), (LANE[ax + '_DIR'], esp(pd)[1]), esp(pd)], ax + '_DIR', SIG)
    # panel plug: through the series resistors, shunts to GND above / below the lines
    for n, key, net, rref, pin in ((1, 'A', 'A_SIG', 'R7', 15), (2, 'B', 'B_SIG', 'R5', 16), (3, 'CTX', 'C_TX', 'R18', 17),
                                   (4, 'CRX', 'C_RX', 'R19', 18)):
        b.track([p('J5', n), (LANE[key], p('J5', n)[1]), (LANE[key], esp(pin)[1]), p(rref, 2)], net, SIG)
    for rref, pin, net in (('R7', 15, 'A_IO'), ('R5', 16, 'B_IO'), ('R18', 17, 'U1_TX'), ('R19', 18, 'U1_RX')):
        b.track([p(rref, 1), esp(pin)], net, SIG)
    b.track([esp(15), p('R21', 2), p('C8', 2)], 'A_IO', SIG)            # under the ESP32
    b.track([esp(16), p('R6', 2)], 'B_IO', SIG)
    b.track([esp(18), p('R20', 2)], 'U1_RX', SIG)
    # ---- right side: power-board plug
    b.track([p('J4', 1), (104.0, p('J4', 1)[1]), (102.4, esp(4, True)[1]), esp(4, True)], 'MAG_IO', SIG)
    for n, lane, pin, net in ((4, 100.0, 5, 'VBAT_SENSE'), (5, 98.4, 6, 'STOP_SENSE'), (6, 96.8, 7, 'SERVO_IO')):
        b.track([p('J4', n), (lane, p('J4', n)[1]), (lane, esp(pin, True)[1]), esp(pin, True)], net, SIG)
    # TOF: SDA lane further from the ESP32 than SCL; pull-ups to 3V3 at the plug
    b.track([p('J6', 3), (94.0, p('J6', 3)[1]), (94.0, esp(8, True)[1]), esp(8, True)], 'SDA', SIG)
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    b.track([p('J6', 4), (92.0, p('J6', 4)[1]), (92.0, esp(9, True)[1]), esp(9, True)], 'SCL', SIG)
    b.track([p('R13', 2), (104.0, p('J6', 4)[1])], 'SCL', SIG)
    # home switches, start, red LED
    for ref, lane, pin, net in (('J7', 88.0, 10, 'X_HOME'), ('J8', 85.6, 16, 'Y_HOME'), ('J9', 83.2, 17, 'START')):
        b.track([p(ref, 1), (lane, p(ref, 1)[1]), (lane, esp(pin, True)[1]), esp(pin, True)], net, SIG)
    b.track([esp(18, True), p('R17', 2)], 'LEDR_IO', SIG)
    b.track([p('R17', 1), (80.8, esp(18, True)[1]), (80.8, p('J10', 1)[1]), p('J10', 1)], 'LEDR_A', SIG)
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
